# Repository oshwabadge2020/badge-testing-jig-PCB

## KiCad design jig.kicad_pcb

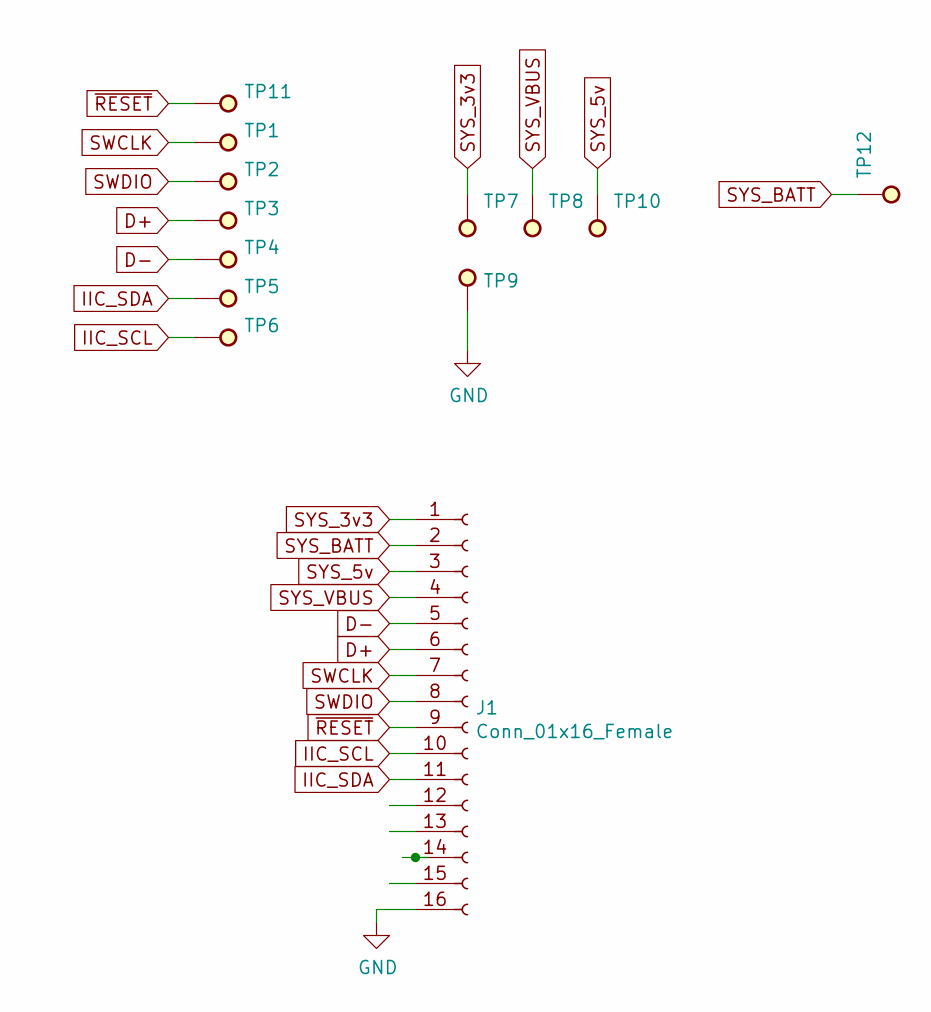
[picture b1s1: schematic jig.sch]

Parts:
J1: Conn_01x16_Female; PinSocket_2x08_P2.54mm_Vertical
TP1, TP2, TP3, TP4, TP5, TP6, TP7, TP8, TP9, TP10, TP11, TP12: TestPoint; Test_Point_Pad_d1.0mm

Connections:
D+: J1.6, TP3.1
D-: J1.5, TP4.1
GND: J1.16, TP9.1
IIC_SCL: J1.10, TP6.1
IIC_SDA: J1.11, TP5.1
SWCLK: J1.7, TP1.1
SWDIO: J1.8, TP2.1
SYS_3v3: J1.1, TP7.1
SYS_5v: J1.3, TP10.1
SYS_BATT: J1.2, TP12.1
SYS_VBUS: J1.4, TP8.1
~RESET: J1.9, TP11.1

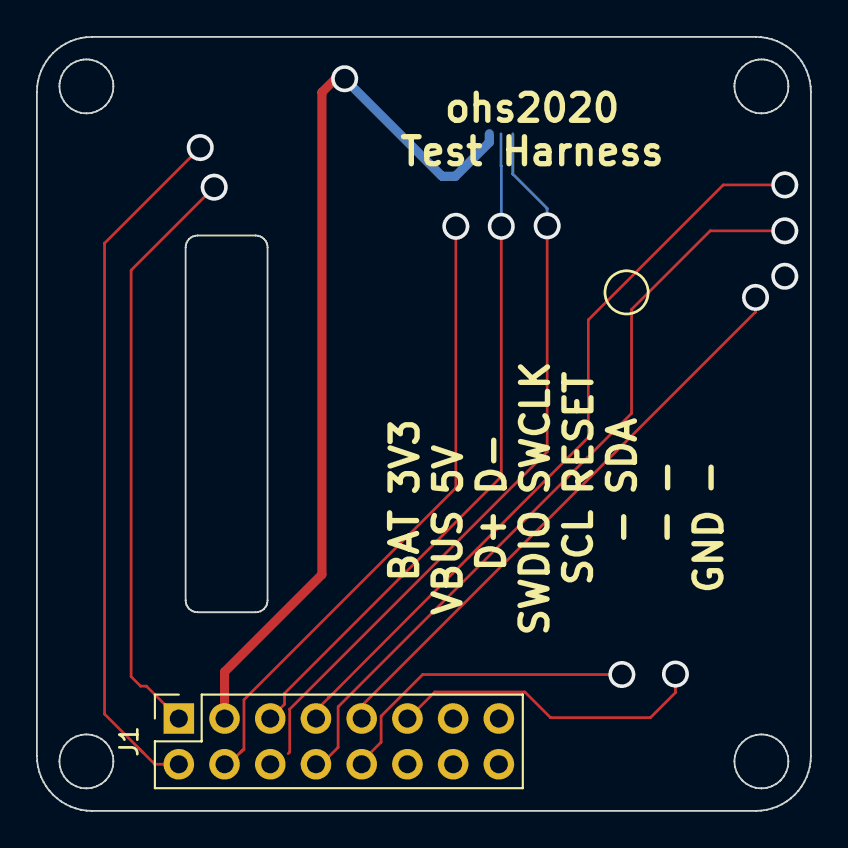
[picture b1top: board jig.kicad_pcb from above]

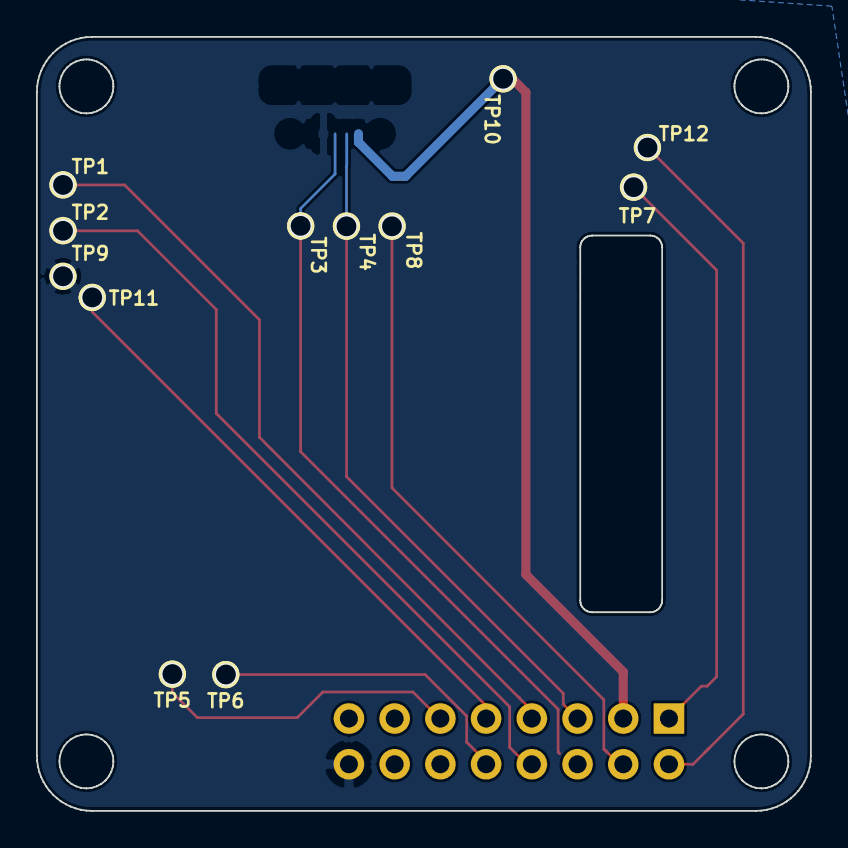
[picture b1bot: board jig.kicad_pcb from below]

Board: 2 copper layers, 43.0 x 43.0 mm, 14 parts (12 on the bottom side), 12 nets.

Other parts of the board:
Ref**: Val**; pcb-top

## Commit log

2020-01-31 test jig
2020-02-05 Test jig for badge
2020-02-05 2060 profile
